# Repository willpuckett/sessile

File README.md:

# 🧽 Sessile

_Sessile_ is a further exploration of "minimal" finger travel.

## 🤔 What Even Is 'Minimal Finger Travel' Anyway?

Probably the least amount of finger travel would be not moving them at all. That
would be 10 keys...

```math
combos_{10\,keys} = \sum_{r=1}^{10} C(10, r) = 1023
```

...yielding **1023** possible combinations.

More realistically, we might consider excluding cross hand combinations so that
modifiers might be used. That would give us

```math
combos_{5\,keys} = \sum_{r=1}^{5} C(5, r) = 31
```

So, with only 5 keys on both hands, and no cross hand combos, we would have a
total of **62** possible keys per layer—more than sufficient.

I wasn't quite ready to take on learning to type on that though, so just
avoiding lateral reaches seemed like a start. 🙃

## ✨ Features

- 🧩 Sessile uses
  [KLP-Lame keycaps](https://github.com/braindefender/KLP-Lame-Keycaps). Larger
  caps may be tight, especially on the bottom row. I was lazy and didn't model
  the tilted keycaps in the rendering, but they're much nicer for the vertical
  combos.

- 🔋 Uses battery LIR1254. **DO NOT substitute LR44.**

- 🔌 The high speed pins were left available for encoders and _could_ be wired
  in a subsequent revision.

- ⚙️ Built for RMK. Configure using [Vial](https://get.vial.today).

## 🏠 Case

A 3D printable case is available in the
[latest release](https://github.com/willpuckett/sessile/releases/latest)! The
case is designed to sit as low as possible and can be secured with a stroke of
glue stick underneath. Case is generated via ergogen with jscad v2 api.
[Try it out](https://github.com/ergogen/ergogen/pull/159) it's testing 10-20x
faster than @jscad/cli@1.

## 📦 Production Files

Ready to manufacture your own board? All production files are included in the
repository:

Includes gerbers, BOM, and CPL files for JLC. Finished boards are ~~available~~
[sold out](https://octule.com/listing/1842172090/sessile) till the next batch.

## 🎨 Origin

_Sessile_ was produced using
[studyofhands](https://github.com/willpuckett/studyofhands).

## 🚀 Firmware

This board is designed for RMK. 😏

### 🦀 RMK

Current RMK build is available in the
[Releases](https://github.com/willpuckett/sessile/releases/latest).

You can build the firmware yourself by cloning this repository and running

```bash
cd rmk && cargo make uf2 --release
```

> [!TIP]
> If you haven't previously used Rust to build software for nRF52840, you may
> need to follow the
> [Setup RMK Environment](https://rmk.rs/guide/user_guide/2-2_local_compilation#setup-rmk-environment)
> instructions.

## 🗺️ Keymap

<div align="center">

Generated with
[keymap-drawer](https://github.com/caksoylar/keymap-drawer/tree/main).

Physical layout imported from KiCad via
[keymap-layout-tools](https://nickcoutsos.github.io/keymap-layout-tools/).

</div>

## 🔌 Matrix Diagram

Sessile uses the following pinout for its matrix:

> [!NOTE]
> Referencing
> [this pinout sheet provided by Seeed](https://files.seeedstudio.com/wiki/XIAO-BLE/XIAO-nRF52840-pinout_sheet.xlsx),
> the only two exposed high speed pins P0_04/SDA/D4 & P0_05/SCL/D5 have been
> left available for possible encoders in a subsequent revision.

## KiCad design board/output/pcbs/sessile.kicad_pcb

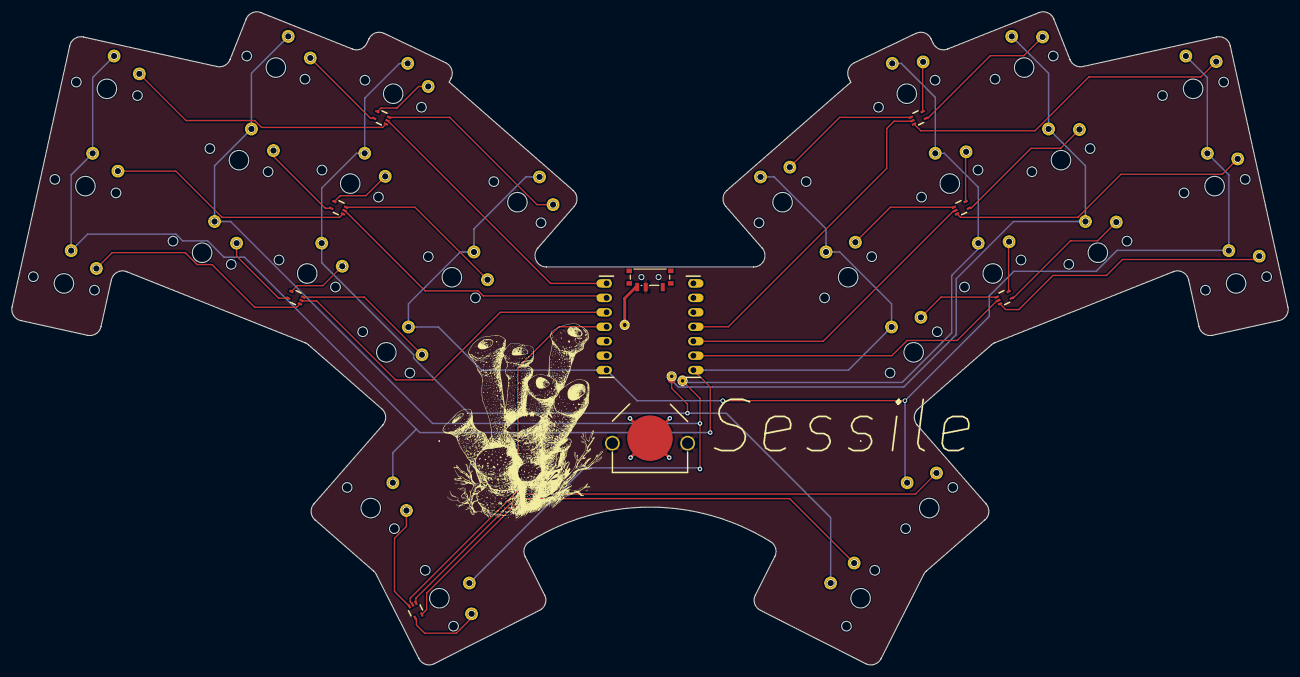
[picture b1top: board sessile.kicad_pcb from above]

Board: 2 copper layers, 224.2 x 114.7 mm, 99 parts (0 on the bottom side), 46 nets.

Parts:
BAT1: CONN-TH_MY-LR44-03-J
D3, D4, D5, D6, D7, D8, D9: UMP1NTR; SOT-353_L2.1-W1.3-P0.65-LS2.3-BL
J1, J2, J3: 0906-2-15-20-75-14-11-0
J4, J5, J6, J7, J8, J9, J10, J11, J12, J13, J14, J15, J16, J17, J18, J19, J20, J21, J22, J23, J24, J25, J26, J27, J28, J29, J30, J31, J32, J33, J34, J35, J36, J37, J38, J39, J40, J41, J42, J43, J44, J45, J46, J47, J48, J49, J50, J51, J52, J53, J54, J55, J56, J57, J58, J59: mill-max-3305-0-15-01-47-XX-10-0
J60, J61: HDR-TH_7P-P2.54-V-F_MF254V-11-07-0743
MCU1: xiao-ble
S1, S2, S3, S4, S5, S6, S7, S8, S9, S10, S11, S12, S13, S14, S15, S16, S17, S18, S19, S20, S21, S22, S23, S24, S25, S26, S27, S28: PG1350_KLP_LAME
SW1: power_switch

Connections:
GND: BAT1.2, J61.2, MCU1.2
NFC0: J2.1, J10.1, J11.1, J12.1, J19.1, J20.1, J21.1, J31.1, MCU1.8, S7.2, S8.2, S9.2, S16.2, S17.2, S18.2, S28.2
NFC1: J3.1, J7.1, J8.1, J9.1, J22.1, J23.1, J24.1, J29.1, MCU1.9, S4.2, S5.2, S6.2, S19.2, S20.2, S21.2, S26.2
P0: D5.2, J60.1, MCU1.18
P1: D4.2, J60.2, MCU1.17
P2: D3.2, J60.3, MCU1.16
P3: D9.2, J60.4, MCU1.15
P4: J60.5, MCU1.14
P5: J60.6, MCU1.13
P6: J13.1, J14.1, J15.1, J16.1, J17.1, J18.1, J30.1, J60.7, MCU1.12, S10.2, S11.2, S12.2, S13.2, S14.2, S15.2, S27.2
P7: J4.1, J5.1, J6.1, J25.1, J26.1, J27.1, J28.1, J61.7, MCU1.7, S1.2, S2.2, S3.2, S22.2, S23.2, S24.2, S25.2
P8: D6.2, J61.6, MCU1.6
P9: D7.2, J61.5, MCU1.5
P10: D8.2, J61.4, MCU1.4
RAW: J1.1, MCU1.21, SW1.3
VBAT: BAT1.1, SW1.2
VCC3: J61.3, MCU1.3
VCC5: J61.1, MCU1.1
index_bottom: D3.3, J41.1, S10.1
index_home: D4.3, J42.1, S11.1
index_top: D5.3, J43.1, S12.1
middle_bottom: D3.4, J38.1, S7.1
middle_home: D4.4, J39.1, S8.1
middle_top: D5.4, J40.1, S9.1
mirror_index_bottom: D6.1, J53.1, S22.1
mirror_index_home: D7.1, J54.1, S23.1
mirror_index_top: D8.1, J55.1, S24.1
mirror_middle_bottom: D6.5, J50.1, S19.1
mirror_middle_home: D7.5, J51.1, S20.1
mirror_middle_top: D8.5, J52.1, S21.1
mirror_pinky_bottom: D6.3, J44.1, S13.1
mirror_pinky_home: D7.3, J45.1, S14.1
mirror_pinky_top: D8.3, J46.1, S15.1
mirror_reachy_default: D9.5, J59.1, S28.1
mirror_ring_bottom: D6.4, J47.1, S16.1
mirror_ring_home: D7.4, J48.1, S17.1
mirror_ring_top: D8.4, J49.1, S18.1
mirror_tucky_default: D9.1, J58.1, S27.1
pinky_bottom: D3.1, J32.1, S1.1
pinky_home: D4.1, J33.1, S2.1
pinky_top: D5.1, J34.1, S3.1
reachy_default: D9.4, J57.1, S26.1
ring_bottom: D3.5, J35.1, S4.1
ring_home: D4.5, J36.1, S5.1
ring_top: D5.5, J37.1, S6.1
tucky_default: D9.3, J56.1, S25.1

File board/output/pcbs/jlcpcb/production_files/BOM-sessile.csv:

Comment,Designator,Footprint,LCSC,Quantity
mill-max-3305-0-15-01-47-XX-10-0,"J10,J11,J12,J13,J14,J15,J16,J17,J18,J19,J20,J21,J22,J23,J24,J25,J26,J27,J28,J29,J30,J31,J32,J33,J34,J35,J36,J37,J38,J39,J4,J40,J41,J42,J43,J44,J45,J46,J47,J48,J49,J5,J50,J51,J52,J53,J54,J55,J56,J57,J58,J59,J6,J7,J8,J9",mill-max-3305-0-15-01-47-XX-10-0,C17370797,56
,SW1,power_switch,C221841,1
HDR-TH_7P-P2.54-V-F_MF254V-11-07-0743,"J60,J61",HDR-TH_7P-P2.54-V-F_MF254V-11-07-0743,C2889988,2
UMP1NTR,"D3,D4,D5,D6,D7,D8,D9",SOT-353_L2.1-W1.3-P0.65-LS2.3-BL,C510065,7
0906-2-15-20-75-14-11-0,"J1,J2,J3",0906-2-15-20-75-14-11-0,C5261048,3
CONN-TH_MY-LR44-03-J,BAT1,CONN-TH_MY-LR44-03-J,C5457116,1

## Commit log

2025-01-09 add study of hands graphic to readme
2025-01-09 add outputs for actual board
2025-01-09 remove python script
2025-01-09 add berylline reference
2025-01-10 re-render production files
2025-01-27 update rmk
2025-02-27 more comma magic
2025-02-27 add keymap
2025-02-27 VGMW keymap
2025-03-11 update rmk (combos!)
2025-03-11 add arcane (magic) key to zmk
2025-03-11 correct directory name
2025-03-11 update keymap
2025-03-30 add matrix diagram
2025-03-30 setting up for module usage
2025-03-31 update self path
2025-03-31 update depends
2025-03-31 change self path
2025-03-31 update for module compatability
2025-04-18 add ich magic
2025-05-15 add stl model
2025-07-01 rmk update
2025-07-04 more rmk
2025-07-04 update to new rmk layer config
2025-07-05 RMK becomes daily driver
2025-07-07 bump rmk and rmk-config versions to 0.7.5 and 0.5.4; update dependencies and adjust tap_hold timing
2025-07-10 add caps light
2025-07-10 add zmk branch
2025-07-11 move zmk to separate branch
2025-07-11 build without battery_adc_pin
2025-08-22 adjust combos
2025-08-22 build with unilateral tap
2025-08-24 one more build
2025-09-15 add .pkgxignore
2025-09-15 change brackets
2025-09-18 add github action
2025-09-22 refactor task names in Makefile.toml and update keyboard configuration
2025-09-22 update build action
2025-09-22 add rust toolchain
2025-09-22 add firmware release
2025-09-22 try cacheing
2025-09-22 getting artiifact path
2025-09-22 improve cacheing
2025-09-22 reorganize build task
2025-09-22 correct file glob
2025-09-22 remove bootloader hex
2025-09-22 update gitignore
2025-09-26 add brackets set
2025-10-11 add battery reporting
2025-10-11 remove some spaces
2025-10-29 add scrolllock configuration to keyboard settings for battery reading
2025-10-29 Bump version to 0.3.0 and update dependencies
    - Updated the version in Cargo.toml from 0.2.0 to 0.3.0.
    - Updated nrf-sdc and nrf-mpsl dependencies to the latest commit (11d5c3c).
    - Upgraded bt-hci dependency version from 0.5 to 0.6.
    - Updated embassy-nrf dependency version from 0.7 to 0.8.
    Refactor keyboard.toml configuration for compatability with PR593
    - Changed input/output pins to row/column pins in the matrix configuration.
2025-10-29 (docs) add dynamic keymap to readme
2025-10-30 (docs) style keymap
2025-10-30 (docs) center keymap
2025-10-30 Add media controls
2025-10-30 switch RCtrl to LCtrl for better terminal compatability
2025-10-31 Added a new info.json file containing layout data for the keymap.
2025-10-31 fix: update path to config file in keymap workflow
2025-10-31 fix: include info.json in keymap workflow paths
2025-10-31 fix: remove empty .pkgxignore file
2025-10-31 update .gitignore and README.md for clarity and additional instructions
2025-10-31 fix: update RMK environment setup link in README
2025-10-31 Update sessile_study.svg dimensions and metadata
    - Changed SVG dimensions from 334mm x 200mm to 236.65063mm x 128.68333mm.
    - Updated document name to "sessile_study.svg".
    - Updated Inkscape version to 1.4.2 (ebf0e940, 2025-05-08).
    - Adjusted Inkscape window properties for better usability.
    - Modified image transformation parameters for improved layout.
2025-10-31 fix: update README formatting and improve clarity of notes
2025-10-31 fix: update keymap to include Bootloader key and remove redundant combo
2025-10-31 fix: improve README clarity and formatting, add links for keycaps and tools
2025-10-31 fix: update keymap workflow comments for clarity
2025-10-31 refactor: clean up project by removing unused Cargo files and Python code
2025-11-01 fix: use ergogen for case creation
2025-11-01 Add GitHub Actions workflow for building and releasing board case
2025-11-01 refactor: update build process and scripts for case generation
2025-11-01 re-touch sessile_study.svg
2025-11-02 modernize jscad situation
2025-11-02 fix: change ergogen test specifier for bun compatability
2025-11-02 fix: update GitHub Actions workflow for case build and release paths
2025-11-02 fix: bump sessile version to 0.3.1
2025-11-02 fix: update release steps in workflows to ensure proper release creation
2025-11-02 fix: remove bun.lock and add it to .gitignore
2025-11-02 docs: update README.md for improved clarity and formatting
2025-11-02 docs: improve formatting in README.md for better readability
2025-11-02 fix: update dev script to use pcbnew directly instead of full path
2025-11-02 fix: simplify convert_case script in package.json for improved clarity
2025-11-06 fix: update edition in Cargo.toml from 2021 to 2024
2025-11-06 feat: add KiBot workflow and configuration for JLCPCB integration
2025-11-06 fix: update KiBot action version and adjust configuration for board variant
2025-11-06 feat: add dummy schematic creation to KiBot workflow and update configuration in sessile.kibot.yaml
2025-11-06 fix: remove unnecessary branches specification and clean up KiBot workflow configuration
2025-11-06 fix: uncomment board and schema parameters in KiBot workflow configuration
2025-11-06 fix: replace repository_dispatch with workflow_dispatch and enhance Docker caching in KiBot workflow
2025-11-06 fix: remove Docker caching steps and update KiBot setup in workflow configuration
2025-11-06 fix: clean up KiBot workflow steps and remove unnecessary commands
2025-11-06 fix: change runner from ubuntu-latest to ubuntu-slim in workflow configurations
2025-11-06 fix: remove man-db configuration steps from KiBot workflow
2025-11-06 fix: move checkout step to the beginning of KIBOT job in workflow
2025-11-06 fix: reorder steps in KIBOT job for proper execution flow
2025-11-06 fix: reorganize KiBot job steps and update runner to ubuntu-latest
2025-11-06 fix: streamline KiBot setup by removing unnecessary Python path setup and adjusting command syntax
2025-11-06 fix: update KiBot workflow to streamline job steps and improve execution flow
2025-11-06 fix: add dummy schematic creation step in KiBot workflow
2025-11-06 fix: remove tag trigger and update dispatch events in KiBot workflow
2025-11-06 fix: remove pull_request trigger from KiBot workflow
2025-11-11 fix: update README and add LICENSE file with Solderpad Hardware License v2.1
2025-11-11 fix: improve formatting and readability in README for case and production files sections
2025-12-04 fix: change workflow runners from ubuntu-latest to ubuntu-slim for efficiency
2025-12-08 fix: update version numbers in package.json and Cargo.toml, and enhance keyboard mappings in keyboard.toml
2025-12-08 fix: update key mappings in keyboard.toml for improved functionality
2026-02-03 add double quote combo

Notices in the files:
README.md:
License: Solderpad Hardware v2.1
